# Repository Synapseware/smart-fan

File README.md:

Smart-Fan
=========

Yet another fan project...

# Projects

## Analog
Simple analog fan controller (on/off) using a TMP35.

## Case Cooling
Smart fan controller using tachometer feedback and either PWM (4-pin) or voltage control (3-pin) and a variety of temperature sensors (analog, 1-wire, etc.).  Used to provide automatic temperature control for things like my printer enclosure for air circulation, inlet air control, etc.

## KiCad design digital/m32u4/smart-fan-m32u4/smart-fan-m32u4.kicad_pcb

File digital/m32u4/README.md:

Arduino Leonardo ATMega32u4
===========================

Based on the m32u4 Leonardo board, this fan controller uses digital one-wire temperature sensors and a simple USB-UART for fan programming.

## Pin mappings
https://www.arduino.cc/en/Hacking/PinMapping32u4
```
Pin Name							Mapped Pin Name
1	PE6 (INT.6/AIN0)				Digital pin 7
2	UVcc							+5V
3	D-								RD-
4	D+								RD+
5	UGnd							UGND
6	UCap							UCAP
7	VUSB							VBus
8	(SS/PCINT0) PB0					RXLED
9	(PCINT1/SCLK) PB1				SCK
10	(PDI/PCINT2/MOSI) PB2			MOSI
11	(PDO/PCINT3/MISO) PB3			MISO
12	(PCINT7/OC0A/OC1C/#RTS) PB7		Digital pin 11 (PWM)
13	RESET							RESET
14	Vcc								+5V
15	GND								GND
16	XTAL2							XTAL2
17	XTAL1							XTAL1
18	(OC0B/SCL/INT0) PD0				Digital pin 3 (SCL)(PWM)
19	(SDA/INT1) PD1					Digital pin 2 (SDA)
20	(RX D1/AIN1/INT2) PD2			Digital pin 0 (RX)
21	(TXD1/INT3) PD3					Digital pin 1 (TX)
22	(XCK1/#CTS) PD5					TXLED
23	GND1							GND
24	AVCC							AVCC
25	(ICP1/ADC8) PD4					Digital pin 4
26	(T1/#OC4D/ADC9) PD6				Digital pin 12
27	(T0/OC4D/ADC10) PD7				Digital Pin 6 (PWM)
28	(ADC11/PCINT4) PB4				Digital pin 8
29	(PCINT5/OC1A/#OC4B/ADC12) PB5	Digital Pin 9 (PWM)
30	(PCINT6/OC1B/OC4B/ADC13) PB6	Digital Pin 10 (PWM)
31	(OC3A/#0C4A) PC6				Digital Pin 5 (PWM)
32	(ICP3/CLK0/)0C4A) PC7			Digital Pin 13 (PWM)
33	(#HWB) PE2						HWB
34	Vcc1							+5V
35	GND2							GND
36	(ADC7/TDI) PF7					Analog In 0
37	(ADC6/TDO) PF6					Analog In 1
38	(ADC5/TMS) PF5					Analog In 2
39	(ADC4/TCK) PF4					Analog In 3
40	(ADC1) PF1						Analog In 4
41	(ADC0) PF0						Analog In 5
42	AREF							AEF
43	GND3							GND
44	AVCC1							AVCC
```

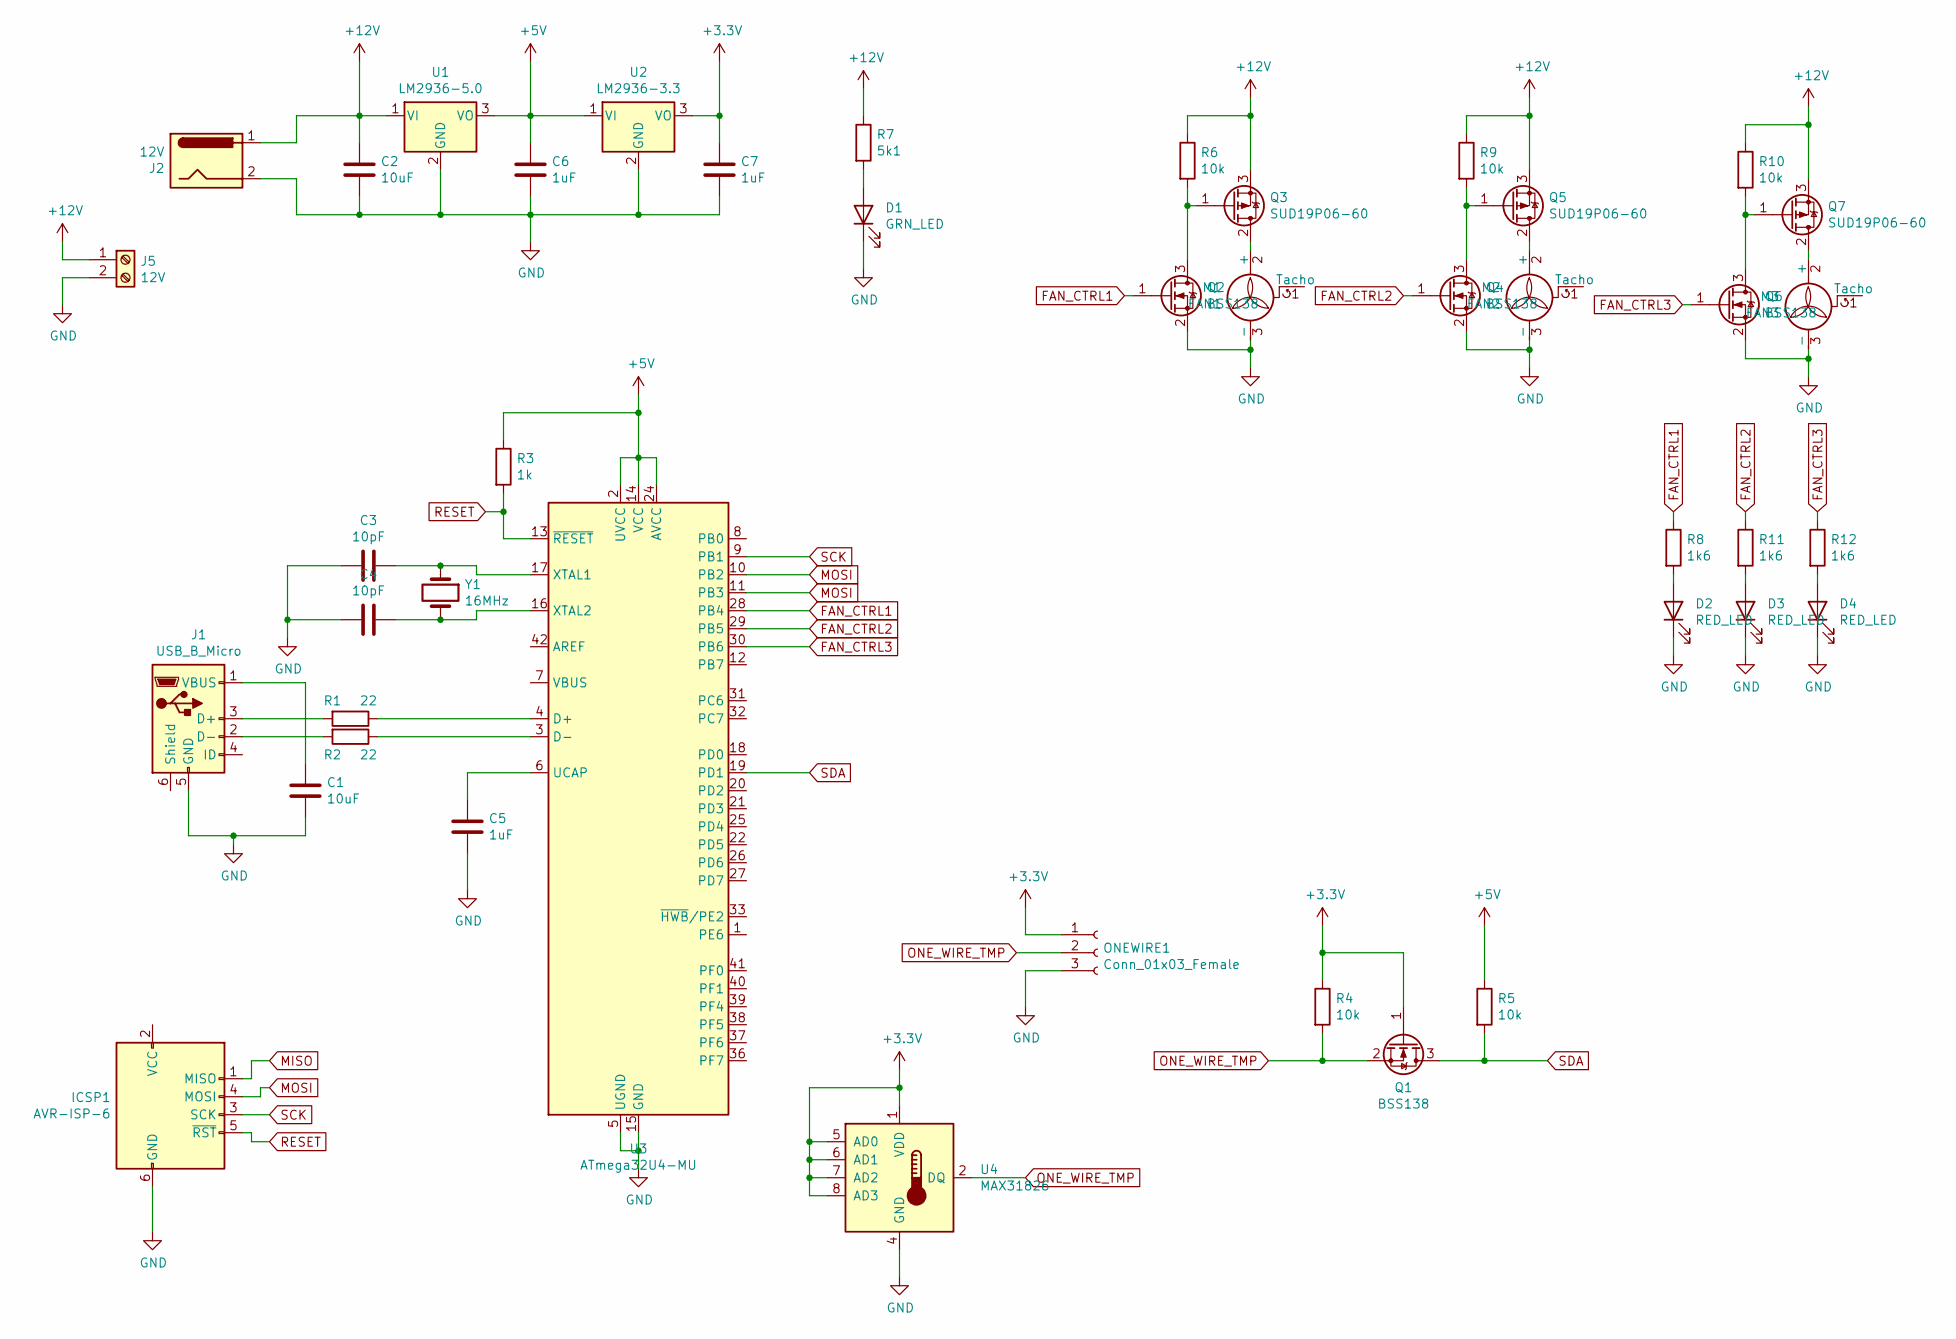
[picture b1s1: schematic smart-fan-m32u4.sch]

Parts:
C1, C2: 10uF; C_0805_2012Metric
C3, C4: 10pF; C_0805_2012Metric
C5, C6, C7: 1uF; C_0805_2012Metric
D1: GRN_LED; LED_0805_2012Metric
D2, D3, D4: RED_LED; LED_0805_2012Metric
ICSP1: AVR-ISP-6; PinHeader_2x03_P2.54mm_Vertical
J1: USB_B_Micro; USB_Micro-B_Amphenol_10104110_Horizontal
J2: 12V; BarrelJack_Horizontal
J5: 12V; TerminalBlock_Phoenix_MKDS-1,5-2-5.08_1x02_P5.08mm_Horizont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
M1: FAN1; FanPinHeader_1x03_P2.54mm_Vertical
M2: FAN2; FanPinHeader_1x03_P2.54mm_Vertical
M3: FAN3; FanPinHeader_1x03_P2.54mm_Vertical
ONEWIRE1: Conn_01x03_Female; PinSocket_1x03_P2.54mm_Vertical
Q1, Q2, Q4, Q6: BSS138; SOT-23
Q3, Q5, Q7: SUD19P06-60; TO-252-2
R1, R2: 22; R_0805_2012Metric
R3: 1k; R_0805_2012Metric
R4, R5, R6, R9, R10: 10k; R_0805_2012Metric
R7: 5k1; R_0805_2012Metric
R8, R11, R12: 1k6; R_0805_2012Metric
U1: LM2936-5.0; SOT-223-3_TabPin2
U2: LM2936-3.3; SOT-223-3_TabPin2
U3: ATmega32U4-MU; QFN-44-1EP_7x7mm_P0.5mm_EP5.2x5.2mm
U4: MAX31826; MSOP-8_3x3mm_P0.65mm
Y1: 16MHz; Crystal_SMD_0603-2Pin_6.0x3.5mm

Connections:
+3V3: C7.1, ONEWIRE1.1, Q1.1 (G), R4.1, U2.3 (VO), U4.1 (VDD), U4.5 (AD0), U4.6 (AD1), U4.7 (AD2), U4.8 (AD3)
+5V: C6.1, R3.1, R5.1, U1.3 (VO), U2.1 (VI), U3.2 (UVCC), U3.14 (VCC), U3.24 (AVCC), U3.34 (VCC), U3.44 (AVCC)
+12V: C2.1, J2.1, J5.1, Q3.3 (S), Q5.3 (S), Q7.3 (S), R6.1, R7.1, R9.1, R10.1, U1.1 (VI)
FAN_CTRL1: Q2.1 (G), R8.1, U3.28 (PB4)
FAN_CTRL2: Q4.1 (G), R11.1, U3.29 (PB5)
FAN_CTRL3: Q6.1 (G), R12.1, U3.30 (PB6)
GND: C1.2, C2.2, C3.2, C4.2, C5.2, C6.2, C7.2, D1.1 (K), D2.1 (K), D3.1 (K), D4.1 (K), ICSP1.6 (GND), J1.5 (GND), J2.2, J5.2, M1.3 (-), M2.3 (-), M3.3 (-), ONEWIRE1.3, Q2.2 (S), Q4.2 (S), Q6.2 (S), U1.2 (GND), U2.2 (GND), U3.5 (UGND), U3.15 (GND), U3.23 (GND), U3.35 (GND), U3.43 (GND), U3.45 (GND), U4.4 (GND)
MISO: ICSP1.1 (MISO)
MOSI: ICSP1.4 (MOSI), U3.10 (PB2), U3.11 (PB3)
unnamed: C1.1, J1.1 (VBUS)
unnamed: C3.1, U3.17 (XTAL1), Y1.1
unnamed: C4.1, U3.16 (XTAL2), Y1.2
unnamed: C5.1, U3.6 (UCAP)
unnamed: D1.2 (A), R7.2
unnamed: D2.2 (A), R8.2
unnamed: D3.2 (A), R11.2
unnamed: D4.2 (A), R12.2
unnamed: J1.2 (D-), R2.2
unnamed: J1.3 (D+), R1.2
unnamed: M1.2 (+), Q3.2 (D)
unnamed: M2.2 (+), Q5.2 (D)
unnamed: M3.2 (+), Q7.2 (D)
unnamed: Q2.3 (D), Q3.1 (G), R6.2
unnamed: Q4.3 (D), Q5.1 (G), R9.2
unnamed: Q6.3 (D), Q7.1 (G), R10.2
unnamed: R1.1, U3.4 (D+)
unnamed: R2.1, U3.3 (D-)
ONE_WIRE_TMP: ONEWIRE1.2, Q1.2 (S), R4.2, U4.2 (DQ)
RESET: ICSP1.5 (~RST), R3.2, U3.13 (~RESET)
SCK: ICSP1.3 (SCK), U3.9 (PB1)
SDA: Q1.3 (D), R5.2, U3.19 (PD1)

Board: 2 copper layers, 43 parts (0 on the bottom side), 30 nets, no tracks yet.

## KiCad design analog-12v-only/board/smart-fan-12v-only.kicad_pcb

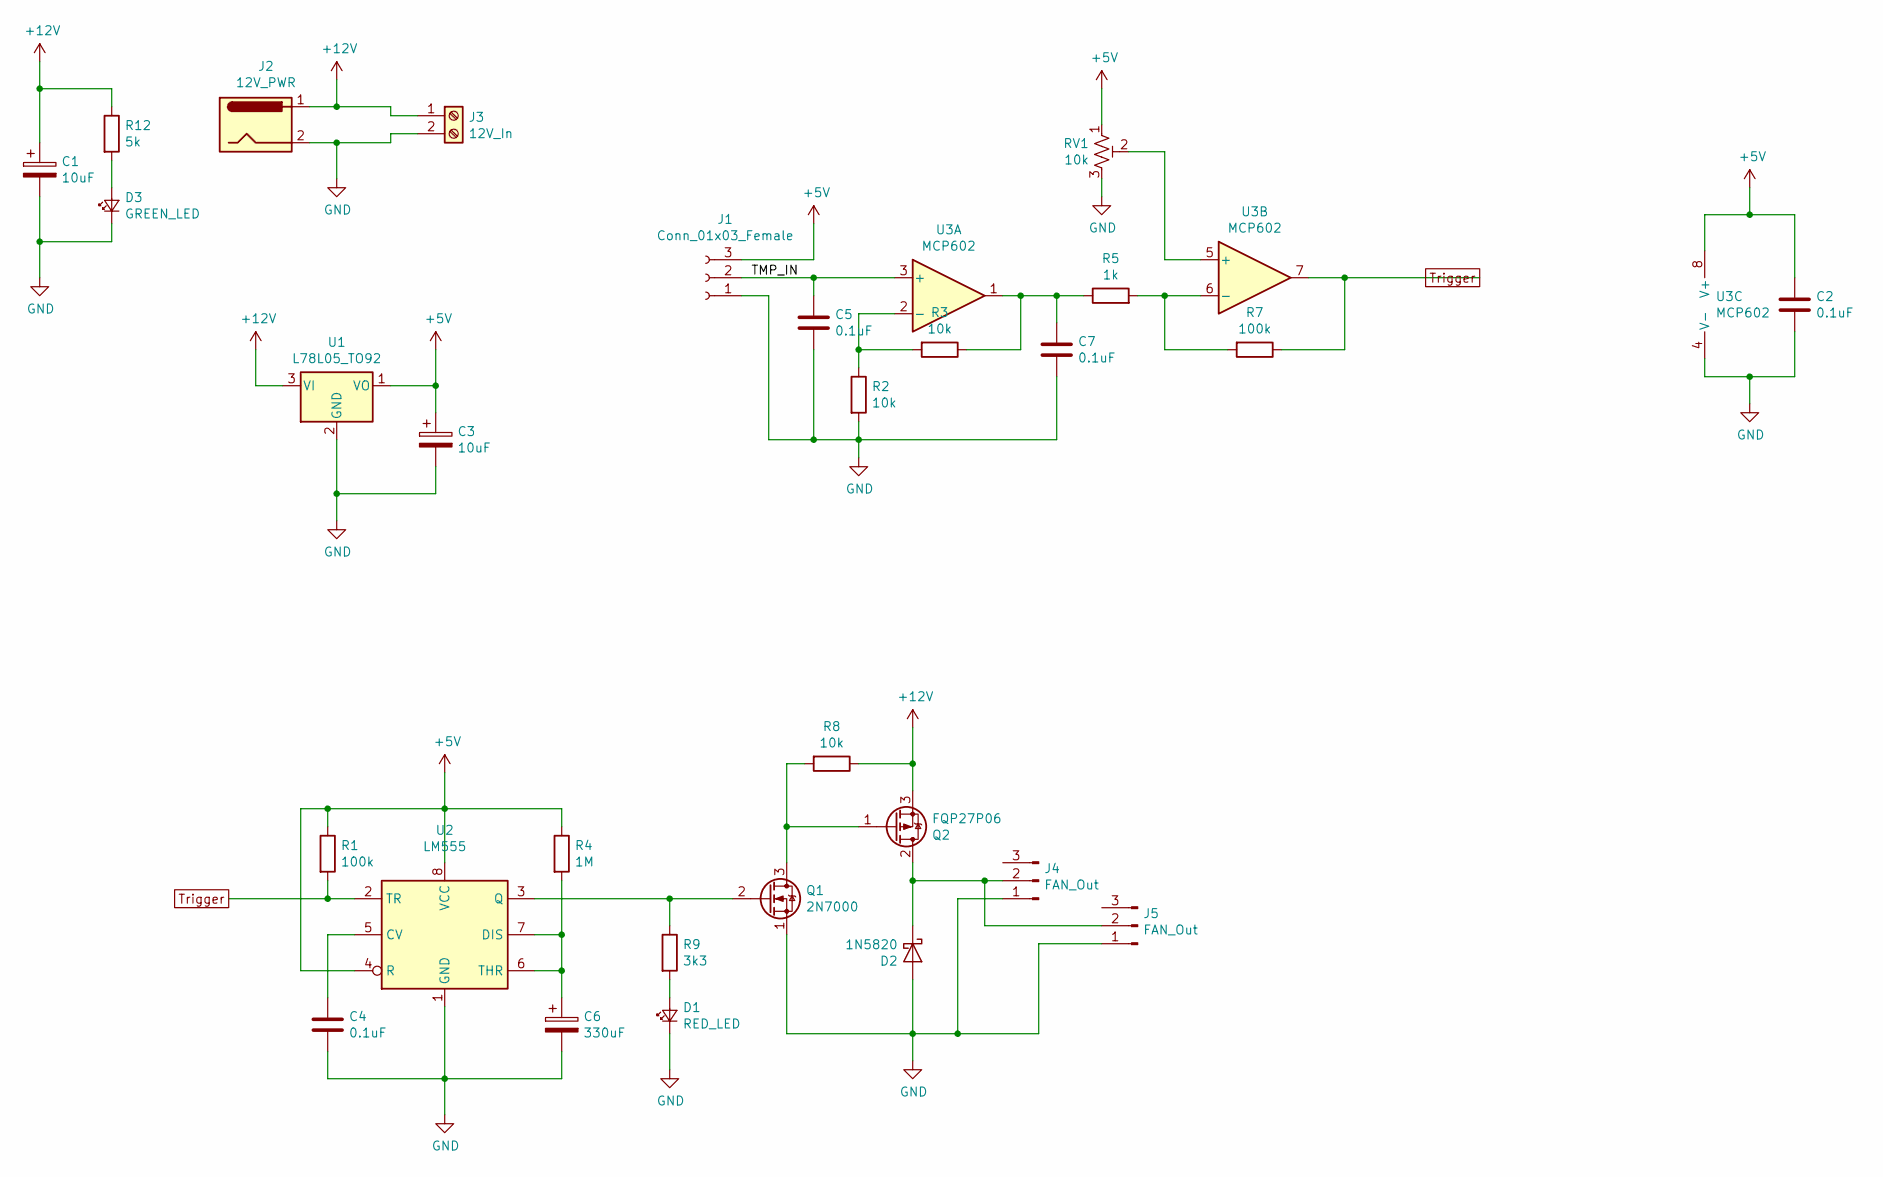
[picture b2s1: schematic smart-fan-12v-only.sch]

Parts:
C1, C3: 10uF; CP_Radial_D5.0mm_P2.00mm
C2, C4, C5, C7: 0.1uF; C_Rect_L4.0mm_W2.5mm_P2.50mm
C6: 330uF; CP_Radial_D7.5mm_P2.50mm
D1: RED_LED; LED_D3.0mm
D2: 1N5820; D_A-405_P2.54mm_Vertical_AnodeUp
D3: GREEN_LED; LED_D3.0mm
J1: Conn_01x03_Female; PinSocket_1x03_P2.54mm_Vertical
J2: 12V_PWR; BarrelJack_Horizontal
J3: 12V_In; TerminalBlock_Phoenix_MKDS-1,5-2_1x02_P5.00mm_Horizontal
J4, J5: FAN_Out; FanPinHeader_1x03_P2.54mm_Vertical
Q1: 2N7000; TO-92_Inline
Q2: FQP27P06; TO-251-3-1EP_Horizontal_TabDown
R1, R7: 100k; R_Axial_DIN0204_L3.6mm_D1.6mm_P2.54mm_Vertical
R2, R3, R8: 10k; R_Axial_DIN0204_L3.6mm_D1.6mm_P2.54mm_Vertical
R4: 1M; R_Axial_DIN0204_L3.6mm_D1.6mm_P2.54mm_Vertical
R5: 1k; R_Axial_DIN0204_L3.6mm_D1.6mm_P2.54mm_Vertical
R9: 3k3; R_Axial_DIN0204_L3.6mm_D1.6mm_P2.54mm_Vertical
R12: 5k; R_Axial_DIN0204_L3.6mm_D1.6mm_P2.54mm_Vertical
RV1: 10k; Potentiometer_Bourns_3266Y_Vertical
U1: L78L05_TO92; TO-92_Inline
U2: LM555; DIP-8_W7.62mm_Socket
U3: MCP602; DIP-8_W7.62mm_Socket

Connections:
+5V: C2.1, C3.1, J1.3, R1.1, R4.1, RV1.1, U1.1 (VO), U2.4 (R), U2.8 (VCC), U3.8 (V+)
+12V: C1.1, J2.1, J3.1, Q2.3 (S), R8.1, R12.1, U1.3 (VI)
/TMP_IN: C5.1, J1.2, U3.3 (+)
GND: C1.2, C2.2, C3.2, C4.2, C5.2, C6.2, C7.2, D1.1 (K), D2.2 (A), D3.1 (K), J1.1, J2.2, J3.2, J4.1, J5.1, Q1.1 (S), R2.2, RV1.3, U1.2 (GND), U2.1 (GND), U3.4 (V-)
unnamed: C4.1, U2.5 (CV)
unnamed: C6.1, R4.2, U2.6 (THR), U2.7 (DIS)
unnamed: C7.1, R3.1, R5.1, U3.1
unnamed: D1.2 (A), R9.2
unnamed: D2.1 (K), J4.2, J5.2, Q2.2 (D)
unnamed: D3.2 (A), R12.2
unnamed: Q1.2 (G), R9.1, U2.3 (Q)
unnamed: Q1.3 (D), Q2.1 (G), R8.2
unnamed: R2.1, R3.2, U3.2 (-)
unnamed: R5.2, R7.2, U3.6 (-)
unnamed: RV1.2, U3.5 (+)
Trigger: R1.2, R7.1, U2.2 (TR), U3.7

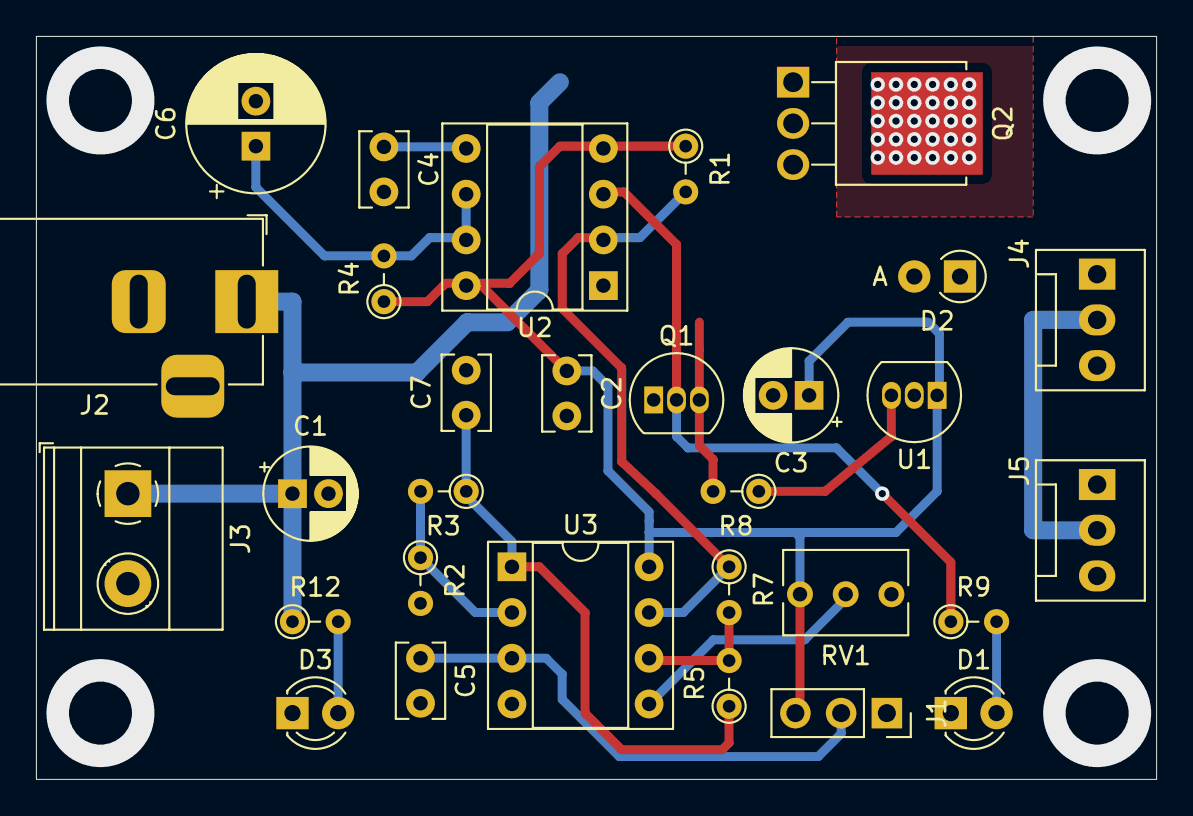
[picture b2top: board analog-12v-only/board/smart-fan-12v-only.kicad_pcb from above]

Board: 2 copper layers, 62.2 x 41.3 mm, 30 parts (0 on the bottom side), 16 nets.

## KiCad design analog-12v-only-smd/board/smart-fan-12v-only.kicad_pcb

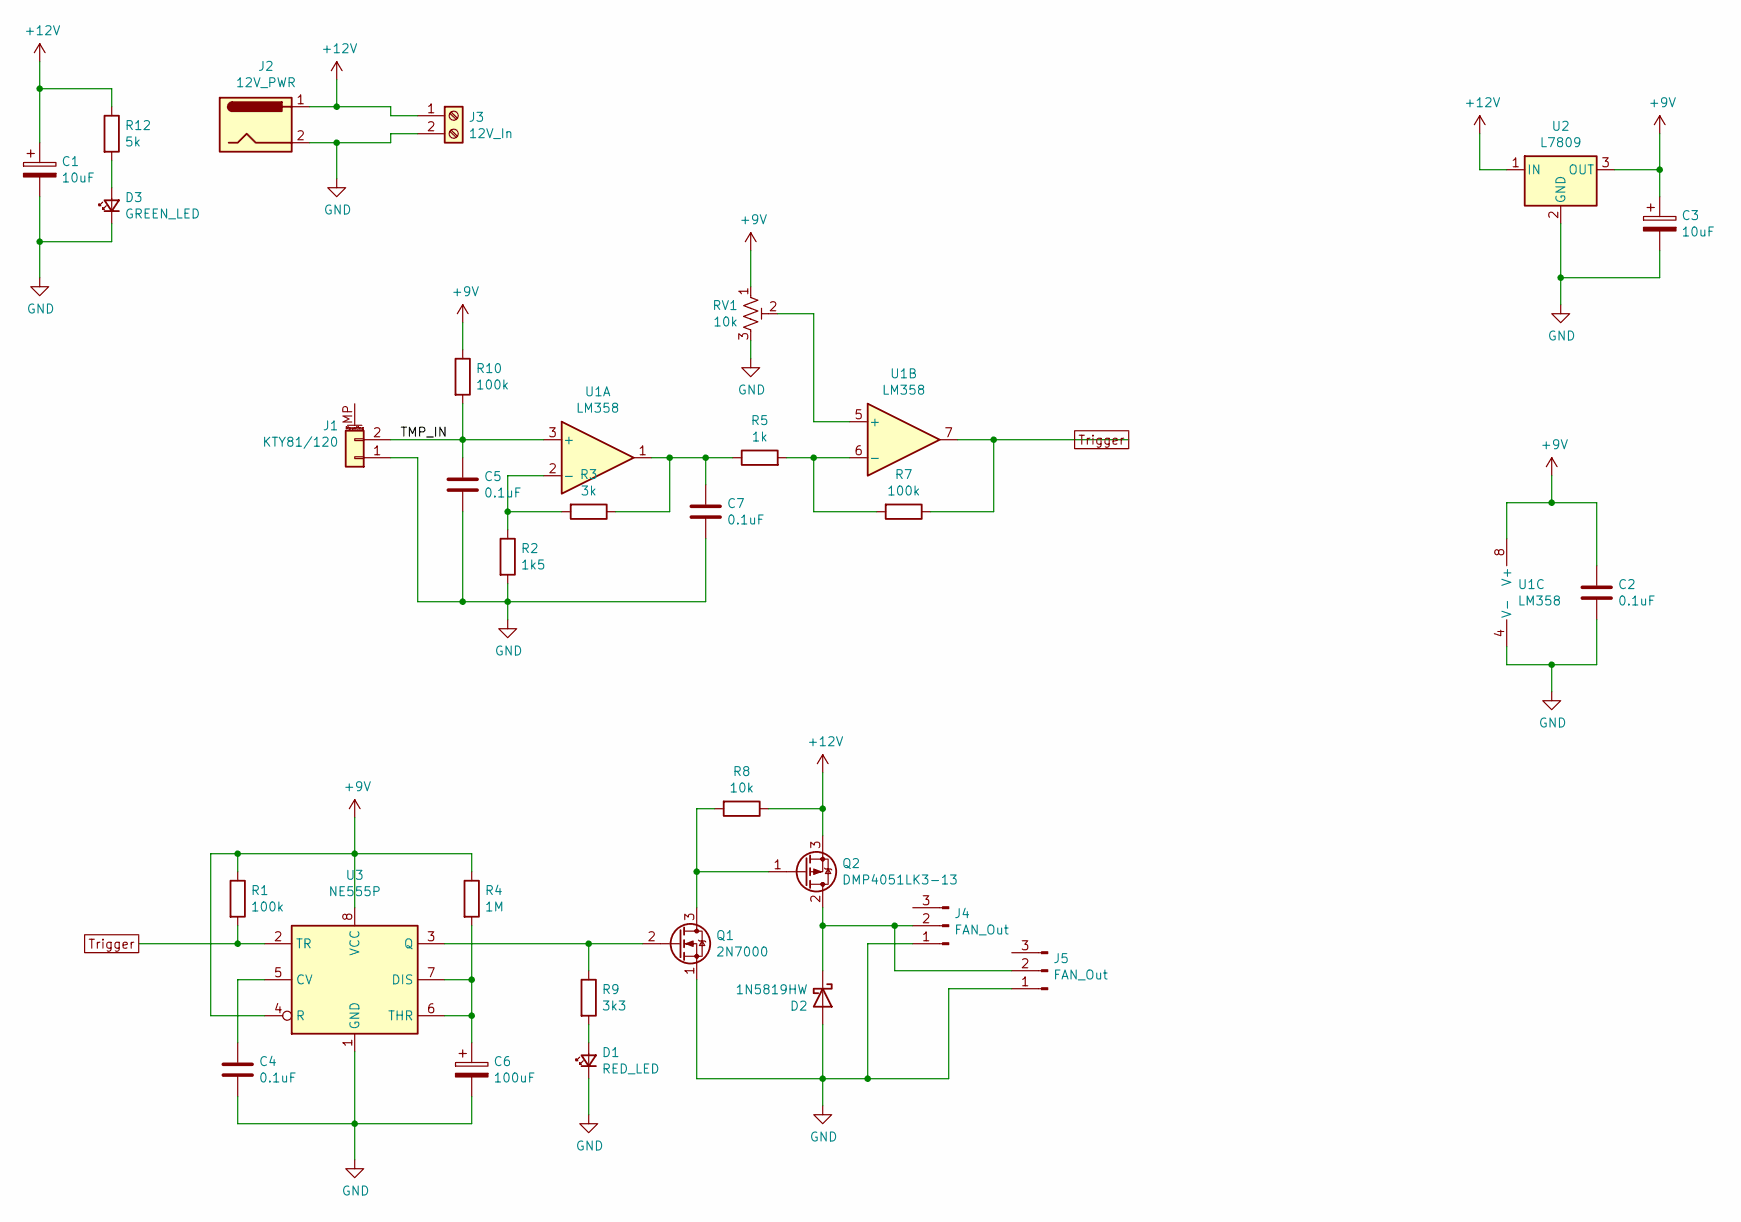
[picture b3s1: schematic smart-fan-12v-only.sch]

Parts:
C1, C3: 10uF; CP_Elec_3x5.3
C2, C4, C5, C7: 0.1uF; C_0805_2012Metric
C6: 100uF; CP_Elec_6.3x4.5
D1: RED_LED; LED_0805_2012Metric
D2: 1N5819HW; D_SOD-123
D3: GREEN_LED; LED_0805_2012Metric
J1: KTY81/120; PinSocket_1x02_P2.54mm_Vertical
J2: 12V_PWR; BarrelJack_Horizontal
J3: 12V_In; TerminalBlock_Phoenix_MKDS-3-2-5.08_1x02_P5.08mm_Horizontal
J4, J5: FAN_Out; FanPinHeader_1x03_P2.54mm_Vertical
Q1: 2N7000; SOT-23
Q2: DMP4051LK3-13; TO-252-2
R1, R7, R10: 100k; R_0805_2012Metric
R2: 1k5; R_0805_2012Metric
R3: 3k; R_0805_2012Metric
R4: 1M; R_0805_2012Metric
R5: 1k; R_0805_2012Metric
R8: 10k; R_0805_2012Metric
R9: 3k3; R_0805_2012Metric
R12: 5k; R_0805_2012Metric
RV1: 10k; Potentiometer_Bourns_3266Y_Vertical
U1: LM358; SO-8_3.9x4.9mm_P1.27mm
U2: L7809; SOT-89-3
U3: NE555P; SO-8_3.9x4.9mm_P1.27mm

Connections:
+9V: C2.1, C3.1, R1.1, R4.1, R10.1, RV1.1, U1.8 (V+), U2.3 (OUT), U3.4 (R), U3.8 (VCC)
+12V: C1.1, J2.1, J3.1, Q2.3 (S), R8.1, R12.1, U2.1 (IN)
/TMP_IN: C5.1, J1.2, R10.2, U1.3 (+)
GND: C1.2, C2.2, C3.2, C4.2, C5.2, C6.2, C7.2, D1.1 (K), D2.2 (A), D3.1 (K), J1.1, J2.2, J3.2, J4.1, J5.1, Q1.1 (S), R2.2, RV1.3, U1.4 (V-), U2.2 (GND), U3.1 (GND)
unnamed: C4.1, U3.5 (CV)
unnamed: C6.1, R4.2, U3.6 (THR), U3.7 (DIS)
unnamed: C7.1, R3.1, R5.1, U1.1
unnamed: D1.2 (A), R9.2
unnamed: D2.1 (K), J4.2, J5.2, Q2.2 (D)
unnamed: D3.2 (A), R12.2
unnamed: Q1.2 (G), R9.1, U3.3 (Q)
unnamed: Q1.3 (D), Q2.1 (G), R8.2
unnamed: R2.1, R3.2, U1.2 (-)
unnamed: R5.2, R7.2, U1.6 (-)
unnamed: RV1.2, U1.5 (+)
Trigger: R1.2, R7.1, U1.7, U3.2 (TR)

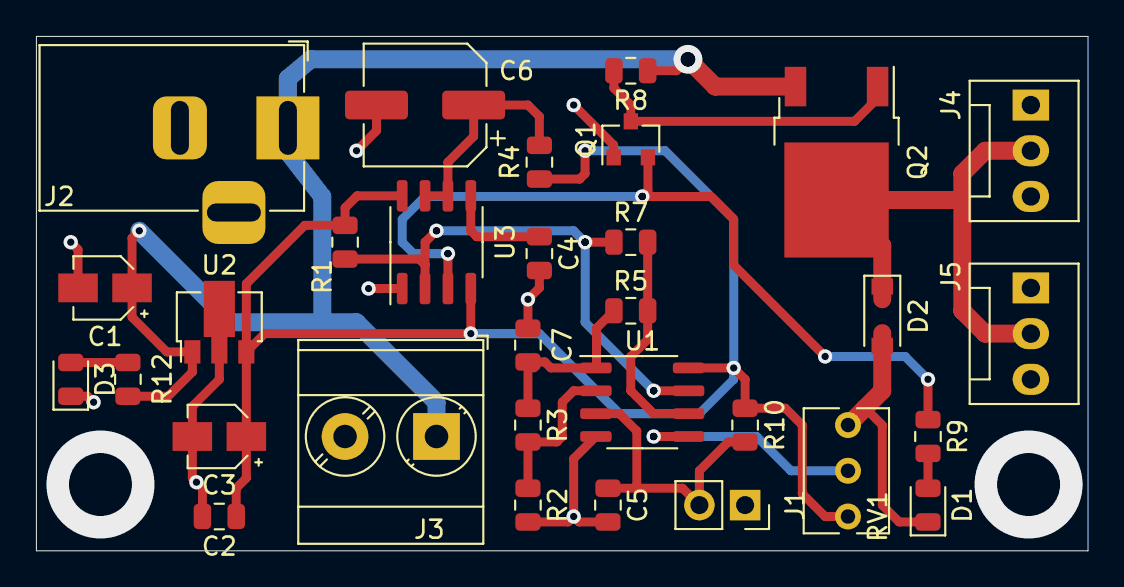
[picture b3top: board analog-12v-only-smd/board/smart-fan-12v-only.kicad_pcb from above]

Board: 2 copper layers, 58.4 x 28.6 mm, 31 parts (0 on the bottom side), 16 nets.

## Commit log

2020-06-15 Working on analog board layout
2020-06-15 Improving board layout
2020-06-17 Board layout complete with ground planes and mounting holes
2020-06-18 Fix up 12v only analog fan controller
2020-06-19 Layout fixes and stable power
2020-06-20 Adding SMD board
2020-06-21 Fix board layout
    Power transistor drain-source swapped
    Flyback diode reversed
2020-06-28 WIP - m32u4 based controller
2020-06-28 Working on layout and adding 2 more fan channels
2020-06-28 Add readme
2020-08-03 WIP: Cleaning up board
